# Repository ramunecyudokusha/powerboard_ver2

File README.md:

# powerboard_ver2
有明高専ロボット研究部電源制御基板2026版

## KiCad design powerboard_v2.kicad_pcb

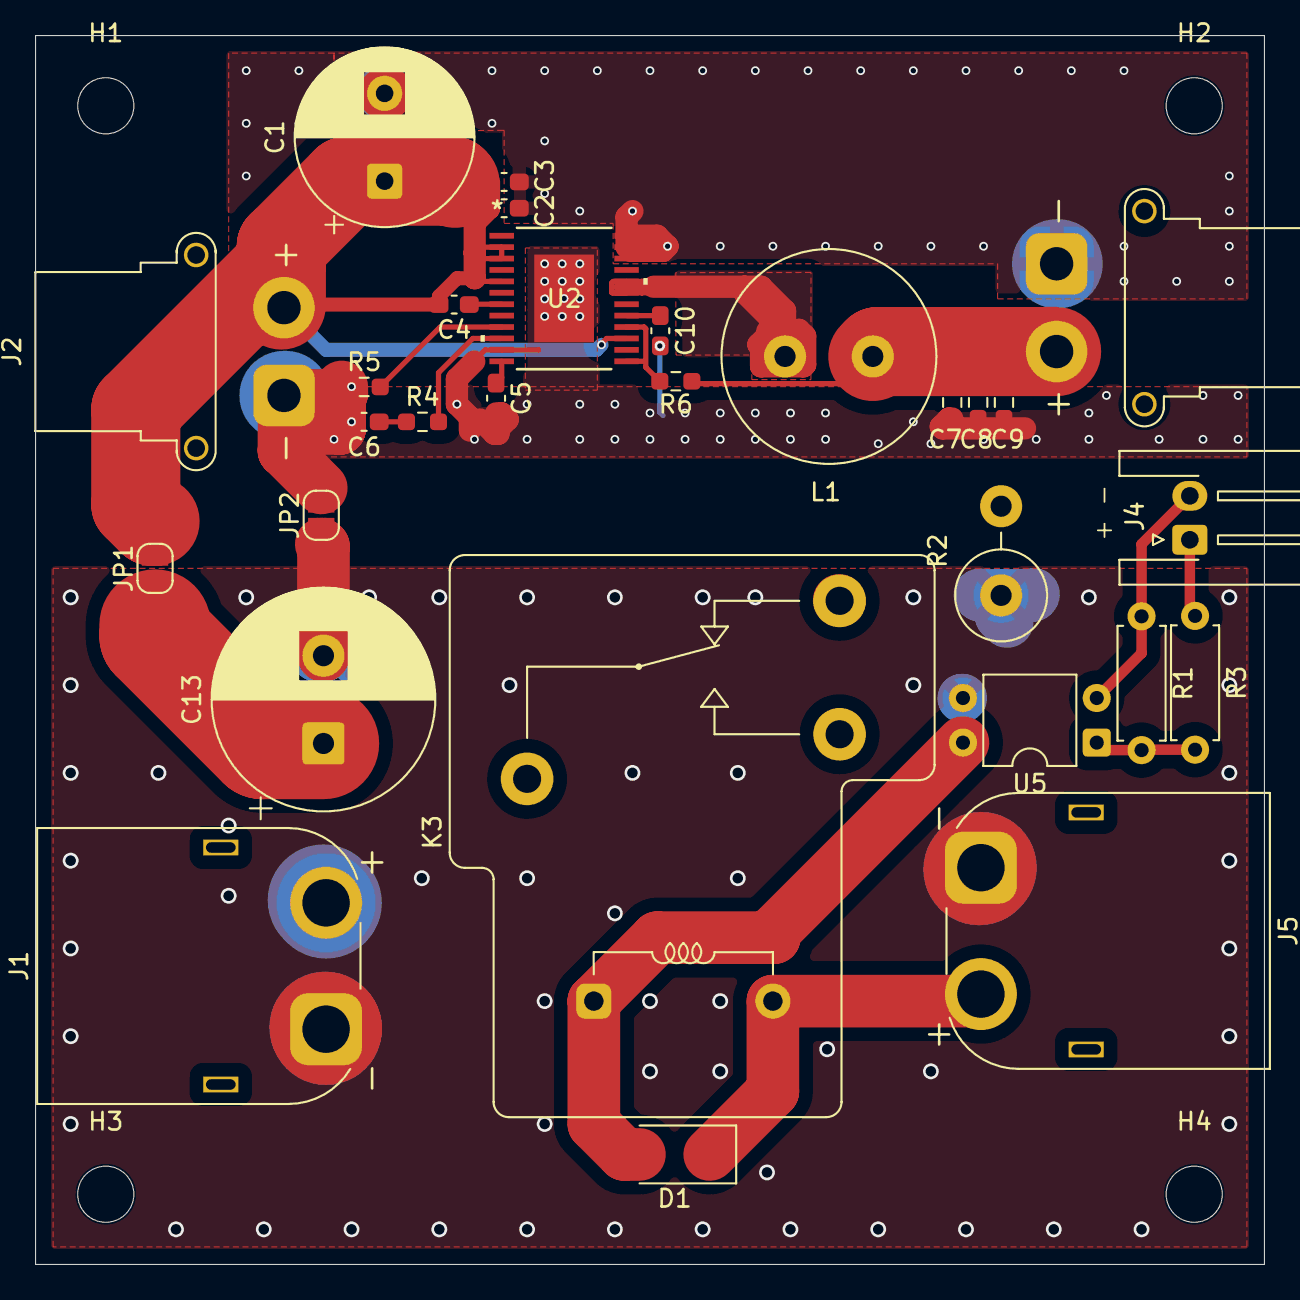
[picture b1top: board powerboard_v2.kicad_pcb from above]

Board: 2 copper layers, 70.0 x 70.0 mm, 33 parts (0 on the bottom side), 19 nets.

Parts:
C1: 220uf; CP_Radial_D10.0mm_P5.00mm
C2, C3: 4.7uf; C_0603_1608Metric_Pad1.08x0.95mm_HandSolder
C4: 0.1uf; C_0603_1608Metric_Pad1.08x0.95mm_HandSolder
C5: 1uf; C_0603_1608Metric_Pad1.08x0.95mm_HandSolder
C6, C10: 2200pf; C_0603_1608Metric_Pad1.08x0.95mm_HandSolder
C7, C8, C9: 22uf; R_0603_1608Metric_Pad0.98x0.95mm_HandSolder
C13: C_Polarized 1000uf; CP_Radial_D12.5mm_P5.00mm
D1: D; D_SMA
H1, H2, H3, H4: MountingHole; MountingHole_3.2mm_M3
J1, J5: Conn_01x02_Pin; AMASS_XT60PW-M_1x02_P7.20mm_Horizontal
J2, J3: Conn_01x02_Pin; AMASS_XT30PW-F_1x02_P2.50mm_Horizontal
J4: Conn_01x02_Pin; JST_XH_S2B-XH-A-1_1x02_P2.50mm_Horizontal
JP1, JP2: SolderJumper_2_Open; SolderJumper-2_P1.3mm_Open_RoundedPad1.0x1.5mm
K3: Relay_SPDT; Relay_SPDT_RAYEX-L90S
L1: 22uH; L_Radial_D12.0mm_P5.00mm_Neosid_SD12k_style2
R1: 1k; R_Axial_DIN0207_L6.3mm_D2.5mm_P7.62mm_Horizontal
R2: 100; R_Axial_DIN0516_L15.5mm_D5.0mm_P5.08mm_Vertical
R3: 70; R_Axial_DIN0207_L6.3mm_D2.5mm_P7.62mm_Horizontal
R4: 20k; R_0603_1608Metric_Pad0.98x0.95mm_HandSolder
R5: 164k; R_0603_1608Metric_Pad0.98x0.95mm_HandSolder
R6: 0; R_0603_1608Metric_Pad0.98x0.95mm_HandSolder
U2: BD99010EFV-ME2; HTSSOP-B24_ROM
U5: TLP785; DIP-4_W7.62mm

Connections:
+3.3V: J4.1, R3.1
+3V3: C7.1, C8.1, C9.1, J3.2, L1.2, R6.2
+7.5V: C1.1, C2.1, C3.1, C4.2, J2.2, JP1.2 (B), U2.2 (PVIN), U2.3 (PVIN), U2.5 (VIN), U2.15 (EN)
+24V: D1.1 (K), J5.2, K3.14, K3.A2
GND: C13.2, J1.1, J5.1, JP2.1 (A), R2.1, U5.3
GND1: J4.2, R1.1, U5.2
GND2: C1.2, C2.2, C3.2, C5.2, C6.2, C7.2, C8.2, C9.2, C10.2, J2.1, J3.1, JP2.2 (B), R5.1, U2.11 (GND), U2.22 (PGND), U2.23 (PGND), U2.24 (PGND), U2.EPAD
unnamed: C6.1, R4.1
unnamed: L1.1, U2.19 (SW), U2.20 (SW)
unnamed: R1.2, R3.2, U5.1
unnamed: R4.2, U2.10 (COMP)
unnamed: R6.1, U2.13 (FPWM), U2.16 (VOUT)
unnamed: C5.1, U2.12 (REG)
unnamed: C10.1, U2.17 (REG_L)
unnamed: R5.2, U2.9 (RT)
unnamed: C4.1, U2.7 (VREGB)
cap out: K3.12, R2.2
photo in: D1.2 (A), K3.A1, U5.4
xt60_out: C13.1, J1.2, JP1.1 (A), K3.11

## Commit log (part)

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2026-03-15 start project
2026-03-16 信号制御部の回路図の作成 駆動部への信号は変更する可能性あり
2026-03-18 くそでかコンデンサを配置
2026-03-19 一応バックアップ
2026-04-11 リレーの外部ライブラリのインポート
2026-04-11 必要部品の配置(フォトカプラ再選定の必要性ありかも？)
2026-04-12 フォトカプラの置き換えとコンデンサと放電回路の作成(未完了)
2026-04-12 マイコン制御部を削除
2026-04-12 フットプリントの割り当て
2026-04-14 回路構成の変更、フットプリントの割り当て、部品配置
2026-04-15 配線前最終版
2026-04-17 ver1かんせい
2026-04-19 製造用出力
2026-05-14 test
    ファイルを置き換えた場合の変化を見る
2026-06-16 改良版作成開始 dcdcの配置
2026-06-20 降圧回路の搭載
    降圧用dcdcなどを置いた 次部品配置
2026-06-22 ver2粗方完成(粗はある)
